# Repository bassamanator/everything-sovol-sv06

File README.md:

# Everything Sovol SV06

A repository containing specifications of the Sovol SV06 3D printer parts, as well as links to aftermarket replacement parts.

You can assume that all information herein is accurate unless stated otherwise.

You can also contribute by making a [pull-request](https://github.com/bassamanator/everything-sovol-sv06/pulls), creating an [issue](https://github.com/bassamanator/everything-sovol-sv06/issues), or starting a [discussion](https://github.com/bassamanator/everything-sovol-sv06/discussions).

## Support Me ❤️

Please ⭐ star this repository! Support [open source](https://en.wikipedia.org/wiki/Open_source), and buy me a .

_Some of the links found on this page may be affiliate links._

# Contents

1. [Initial Setup Steps](./docs/initial-setup-checks.md)
2. [Print Head](./docs/hotend.md)
   - [PCB](./docs/hotend.md#pcb)
   - [Hotend](./docs/hotend.md#hotend)
     - [Heater Cartridge](./docs/hotend.md#heater-cartridge)
     - [Thermistor](./docs/hotend.md#thermistor)
     - [Heatbreak](./docs/hotend.md#heatbreak)
     - [Nozzle](./docs/hotend.md#nozzle)
   - [Filament Sensor](./docs/hotend.md#filament-sensor)
   - [Probe](./docs/hotend.md#probe)
   - _Fans_
   - [Extruder](./docs/hotend.md#extruder)
3. [Motherboard](./docs/motherboard.md)
4. [Motion System](./docs/motion-system.md)
   - [Lead Screws](./docs/motion-system.md#lead-screws)
   - [POM Nuts](./docs/motion-system.md#pom-nuts)
   - [Linear Motion Guide Rods](./docs/motion-system.md#linear-motion-guide-rods)
   - [Linear Bearings](./docs/motion-system.md#linear-bearings)
   - [Z Axis Couplers](./docs/motion-system.md#z-axis-couplers)
   - [Belts](./docs/motion-system.md#belts)
   - [Stepper Motors](./docs/motion-system.md#stepper-motors)
5. [Power Supply](./docs/power-supply.md)
6. [How To 🛠️](./docs/how-to.md)
7. [Links](./docs/links.md)
8. [Sample Prints 🍰](./images/prints/README.md)
9. [Printed Upgrades 🏗️](./parts/README.md#printed-parts)
10. [Modifications 🪚](https://github.com/bassamanator/everything-sovol-sv06/tree/mods)

# Stay Up-to-Date

This repository is a work in progress. Watch for updates:

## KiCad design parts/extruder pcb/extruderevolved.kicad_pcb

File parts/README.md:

# Printed Upgrades

Please use common sense regarding material choice. If you're printing something that is touching the heated bed or near the hotend, use `PETG`/`ABS`/`other high temperature filament`.

## Essential

### Bed Cable Strain Relief at the Motherboard Enclosure

I no longer recommend a part for this, as I did previously. I think it actually strains the cable which eventually leads to damaged wires, as I experienced.

### Bed Cable Strain Relief at the Bed

- Designer: [@braga3dprint](https://www.printables.com/@braga3dprint)
- Printer: SV06
- [Source](https://www.printables.com/model/452682-sovol-sv06-strain-relief)
- [Download](https://www.printables.com/model/452682-sovol-sv06-strain-relief/files)
- I prefer the flat version as it perfectly supports the cable and doesn't interfere with my part cooling duct.
- After you get the part in place, make sure your bed can move freely without the bed cable snagging at the printer base extrusions.

## Useful

### Frame Mounting Solution

- Designer: [@bassamanator](https://www.printables.com/@bassamanator)
- Printer: SV06 / Plus
- Download from [here](https://www.printables.com/model/431736-sovol-sv06plus-frame-mounting-solution-2040-extrus).

### Part Cooling Fan Duct

- Designer: [taeky](https://cults3d.com/en/users/taeky/3d-models)
- Printer: SV06 (taeky has a Plus version as well).
- **This is a paid model**.
- There is a V2 of this model as well, but the performance according to the designer is the same. I prefer this version because it holds the duct more securely to the extruder assembly.
- [Sovol SV06 fan duct 5015 - CFD optimized](https://cults3d.com/:1021376)

- Designer: [Leander Perez Blanco](https://www.printables.com/@LeanderPerezB_802715)
- Printer: SV06.
- I have not tested this duct yet, but it is CFD optimized as well.
- There is a 1 fan version as well.
- [The Amonite - Sovol SV06 Fan Duct Dual 5015 Blower Fan V4 ](https://www.printables.com/model/543502-the-amonite-sovol-sv06-fan-duct-dual-5015-blower-f)

### Extrusion Seals

- Designer: [@bassamanator](https://www.printables.com/@bassamanator)
- Printer: SV06 / Plus
- Download from [here](https://www.printables.com/model/385359-sovol-sv06plus-extrusion-seal).

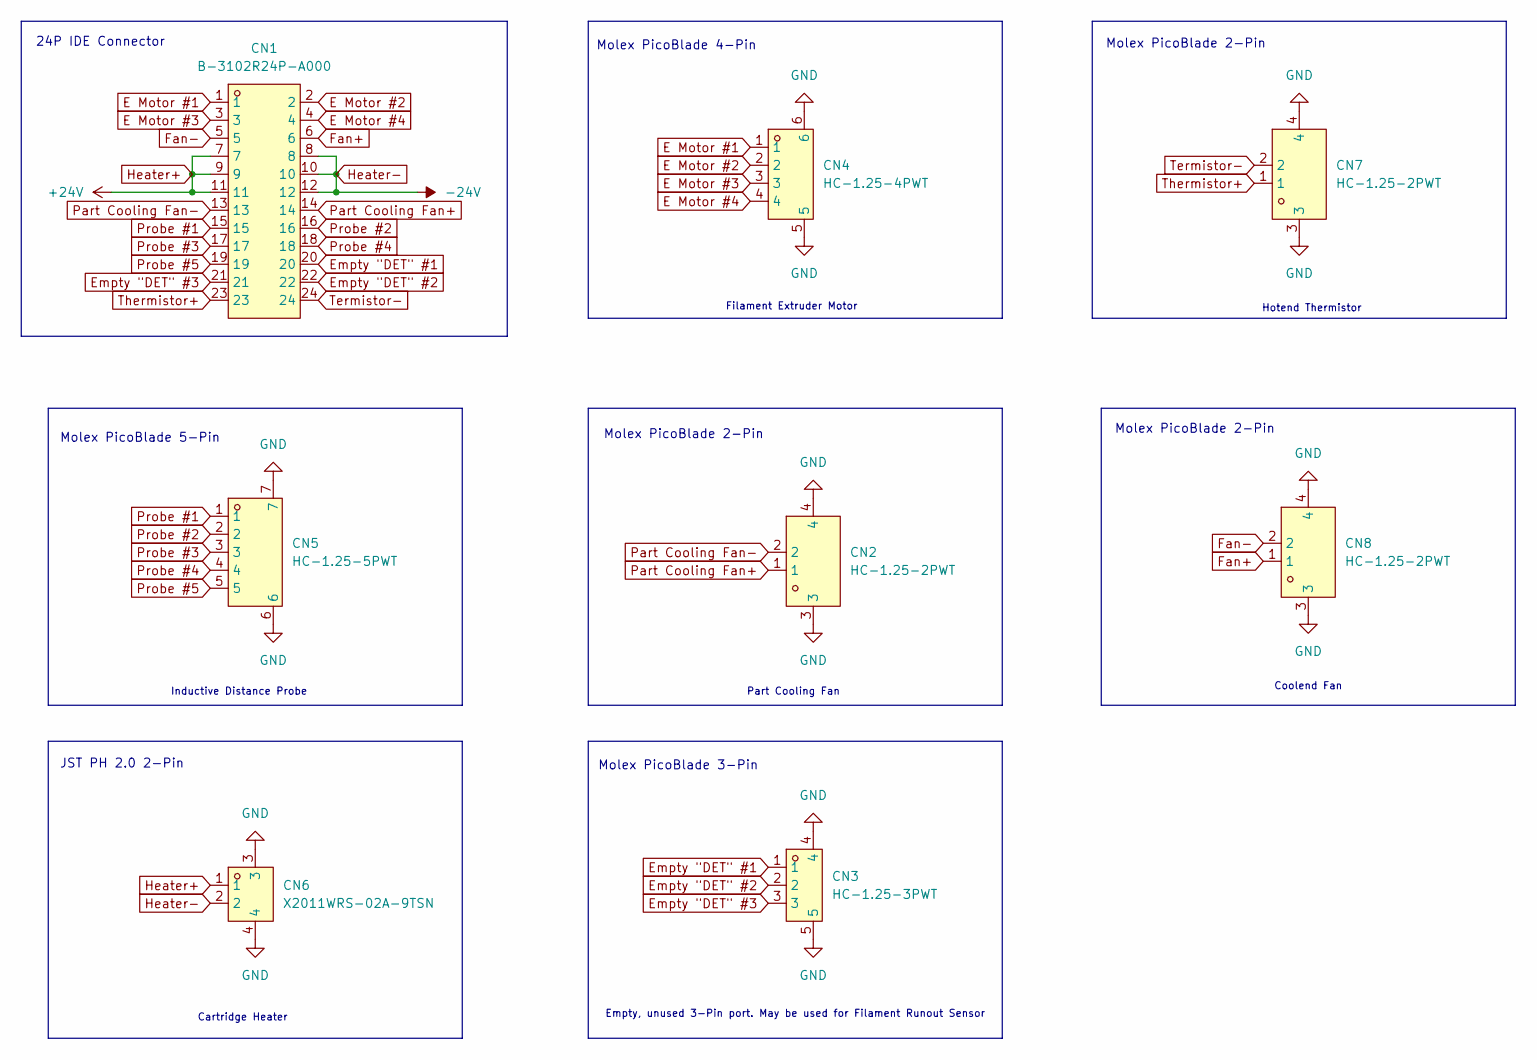
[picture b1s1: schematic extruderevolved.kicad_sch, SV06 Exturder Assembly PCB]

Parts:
CN1: B-3102R24P-A000; IDC-TH_24P-P2.00_B-3102R24P-A000; LCSC Part C383593
CN2, CN7, CN8: HC-1.25-2PWT; CONN-SMD_2P-P1.25-HC-1.25-2PWT; LCSC Part C2845379
CN3: HC-1.25-3PWT; CONN-SMD_HC-1.25-3PWT; LCSC Part C2845380
CN4: HC-1.25-4PWT; CONN-SMD_4P-P1.25-HC-1.25-4PWT; LCSC Part C2845381
CN5: HC-1.25-5PWT; CONN-SMD_5P-P1.25_HCTL_HC-1.25-5PWT; LCSC Part C2845382
CN6: X2011WRS-02A-9TSN; CONN-SMD_2P-P2.00_XKB_X2011WRS-02A-9TSN; LCSC Part C571320

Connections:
E Motor #1: CN1.1, CN4.1
E Motor #2: CN1.2, CN4.2
E Motor #3: CN1.3, CN4.3
E Motor #4: CN1.4, CN4.4
Empty "DET" #1: CN1.20, CN3.1
Empty "DET" #2: CN1.22, CN3.2
Empty "DET" #3: CN1.21, CN3.3
Fan+: CN1.6, CN8.1
Fan-: CN1.5, CN8.2
GND: CN2.3, CN2.4, CN3.4, CN3.5, CN4.5, CN4.6, CN5.6, CN5.7, CN6.3, CN6.4, CN7.3, CN7.4, CN8.3, CN8.4
Heater+: CN1.7, CN1.9, CN1.11, CN6.1
Heater-: CN1.8, CN1.10, CN1.12, CN6.2
Part Cooling Fan+: CN1.14, CN2.1
Part Cooling Fan-: CN1.13, CN2.2
Probe #1: CN1.15, CN5.1
Probe #2: CN1.16, CN5.2
Probe #3: CN1.17, CN5.3
Probe #4: CN1.18, CN5.4
Probe #5: CN1.19, CN5.5
Termistor-: CN1.24, CN7.2
Thermistor+: CN1.23, CN7.1

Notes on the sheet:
24P IDE Connector
Molex PicoBlade 5-Pin
Molex PicoBlade 4-Pin
Molex PicoBlade 2-Pin
JST PH 2.0 2-Pin
Inductive Distance Probe
Empty, unused 3-Pin port. May be used for Filament Runout Sensor
Part Cooling Fan
Filament Extruder Motor
Coolend Fan
Molex PicoBlade 3-Pin
Cartridge Heater
Hotend Thermistor

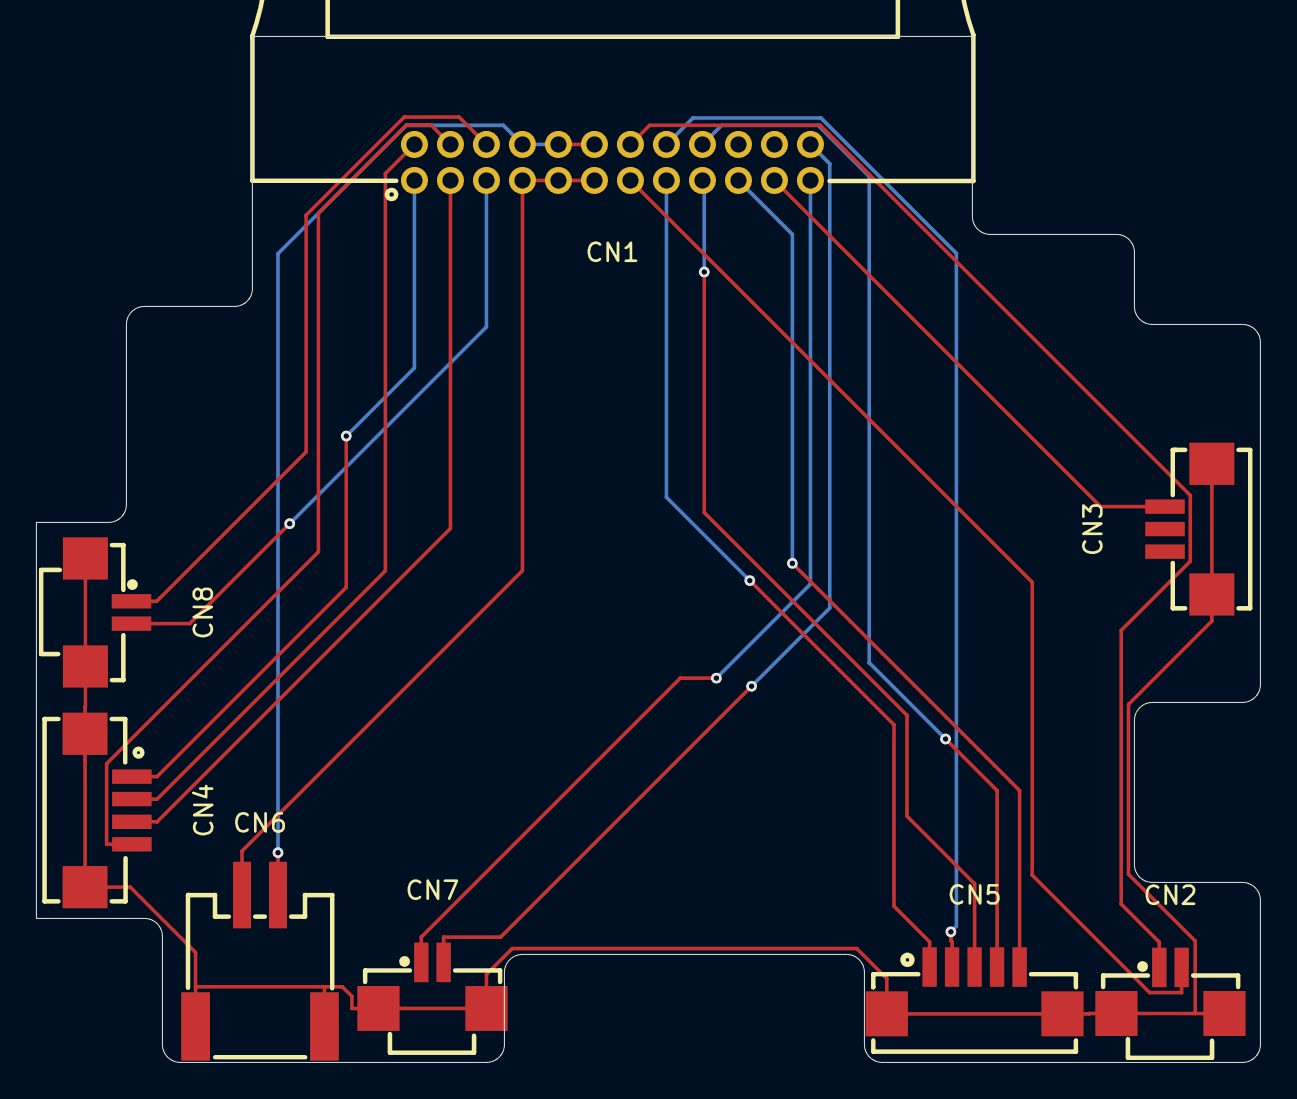
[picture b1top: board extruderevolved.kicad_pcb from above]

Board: 2 copper layers, 68.0 x 57.0 mm, 8 parts (0 on the bottom side), 21 nets.

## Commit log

2023-02-19 Changes.
2023-02-19 More changes.
2023-02-20 Adjusted README.md.
2023-02-22 Added motherboard picture.
2023-02-23 Added sovol repos.
2023-02-26 edited the readme.md
2023-02-27 Eoldev-Terry added lead screw and rod information to README.md (#6)
2023-02-28 Updated to-do list.
2023-03-03 Added Z coupler specs. Other styling changes in lead screw/rod section.
2023-03-03 More to do items.
2023-03-04 Heatblock specs and pictures.
2023-03-04 Heatblock spex and pictures.
2023-03-04 Heatblock spec and photos.
2023-03-05 13mm between the centers of the holes.
    It's looks like 13mm between the centers of the holes.
2023-03-05 Heatbreak spec and pictures.
    Heatbreak spec and pictures.
2023-03-05 Heatbreak spec and pictures.
    22mm long.
2023-03-05 Heatbreak spec and pictures.
    22mm.
2023-03-07 Edited images in Heatblock section.
2023-03-08 Updated to do list.
2023-03-13 Organized hotend section. Added filament sensor information.
2023-03-13 Added links for filament sensors.
2023-03-14 Updated filament sensor section.
2023-03-15 Updated runout sensor section.
2023-03-15 Added how to cable section; filament sensor.
2023-03-15 Added some random prints.
2023-03-19 Added PSU info.
2023-03-20 Update README.md
    Heatblock section.
2023-03-21 Added other psu cable pics.
2023-03-22 Added Heater, Thermistor and heatblock specifications
2023-03-22 Fixed formatting, added aftermarket options
2023-03-22 Fixed typo with M6 block, added how to use M6 nozzle instead of MK8
2023-03-22 Added Silicone Sock image
2023-03-22 Changed cartridge heater voltage to 24V from 12V and added link to source
2023-03-26 Update README.md
    Someone in the Reddit Sovol forum caught this. I checked my notes and the user was correct - it should read 355mm for X length.
2023-03-26 Added information for the heater cartridge mounting and removal
2023-03-28 Merging LimesKey-main: too many changes to enumerate.
2023-03-29 Correction to X length of rod (#20)
    Someone in the Reddit Sovol forum caught this. I checked my notes and the user was correct - it should read 355mm for X length.
2023-03-29 Added new thermistor aftermarket option as per request
2023-04-02 Added jump to sections.
2023-04-02 Fixed section links.
2023-04-02 Added useful parts section.
2023-04-02 Just some renaming.
2023-04-02 Fixed spelling, added useful prints section.
2023-04-02 Update README.md
    Removed to do section; taking up too much room, and not necessary.
2023-04-02 Updated outline.
2023-04-04 Added more sample prints.
2023-04-04 Confirmed extruder motor connection.
2023-04-09 Added psu model.
2023-04-09 Fixed XT60H model.
2023-04-09 Update README.md
    Fixed PSU table.
2023-04-20 Added probe section.
2023-04-20 Added link to purchase probe.
2023-04-20 Outline adjust.
2023-04-20 Probe picture size adjust.
2023-05-03 Options for heater cartridge and thermistor
    The thermistor and heater cartridge seem to be the same ones used on the Ender 3 S1 (Pro)
2023-06-12 Deleted many images. Added url to images.
2023-06-12 Prettified readme. Spelling fixes.
2023-06-14 Heatblock aftermarket link added.
2023-07-17 Adjust vscode project colours.
2023-08-01 Update README.md
    Thermistor section.
2023-08-01 Update README.md
    Heatbreak section notes.
2023-08-01 Update nozzle section.
2023-08-01 Update heatbreak section.
2023-08-01 Simplify heatblock section.
2023-08-01 Adjusted hierarchy.
2023-08-01 Adjusted layout, outline, hierarchy.
2023-08-01 Added link to purchase z coupler.
2023-08-01 Adjust Motherboard section.
2023-08-01 Adjust README.
2023-08-07 Add PSU Internal Fan Cable Connector specs.
2023-08-11 Adjust README.md: probe.
2023-08-11 Adjust README.md: fix heater cartridge wattage; add linear bearing specs.
2023-08-11 Create LICENSE
2023-08-11 Update issue templates
2023-08-12 Added stepper motor section; needs adjustement.
2023-08-12 Adjust Linear Bearings section.
2023-08-20 Added Plus nozzle info.
2023-08-24 Add more useful prints.
2023-08-26 Adjust Printed Parts section.
2023-08-26 Add initial steps section.
2023-08-26 Adjust initial steps.
2023-08-26 Create initialsteps.md.
2023-08-26 Adjust settings.
2023-08-30 Create howto.md. Add calibrate esteps.
2023-09-01 Adjust parts/README.md.
2023-09-01 Adjust parts/README.md. Add Y-axis stepper motor max height.
2023-09-01 Adjust parts/README.md: nozzle change.
2023-09-01 Include e-steps calibration tool.
2023-09-06 Add smooth idler specs.
2023-09-07 Adjust esteps howto.
2023-09-10 Add icons to readme outline. Add sample print.
2023-09-10 Update Update prints/README.md.
2023-10-14 Update README.md
    Newer heatblocks come with 3mm thermistor hole.
2023-10-23 added beacon tutorial
2023-10-23 added safe zone example
2023-10-23 added newline
2023-10-23 fixed spelling errors
2023-11-09 Update README.md
    Adjust resource links
2023-11-10 Add another option for filament sensor
2023-11-10 Fixup
2023-11-10 Add printer.cfg configuration for force_move command
2023-11-11 Update README.md
    Add mods link
2023-11-13 Added beacon probe setup (#32)
    * added beacon tutorial
    * added safe zone example
    * added newline
    * fixed spelling errors
    * Add printer.cfg configuration for force_move
    command
2023-11-13 Adjust mods readme.
2023-11-13 Adjust readme: remove beacon mod from main.
2023-11-14 Adjust filament sensor section.
2023-11-14 Adjust howto.md.
2023-11-23 Update howto.md.
2023-12-16 Add 3dtouch.
2023-12-16 Adjust readme mods.
2023-12-17 Update README.md
    Steppers
2023-12-24 Update howto.md
    Add sovol tech support playlist
2024-01-26 Adjust steppers.
2024-01-26 Adjust sections: lead screws, steppers.
2024-01-28 Adjust psu cable image.
2024-03-05 Add belt section.
2024-03-05 Adjust belts.
2024-03-06 Update howto.md: explain input shaping.
2024-03-06 Adjust parts readme.
2024-03-09 Add extruder section.
2024-03-29 Adjust outline, parts/README.md.
2024-03-29 Update README.md
    Added picture for ribboncable-pinout for probe
2024-03-29 Update README.md
    Uploaded pinoutribboncable.png and updated README.MD
2024-03-29 Probe pinout on ribbon-cable (#44)
    * Update README.md
    Added picture for ribboncable-pinout for probe
    * Add files via upload
    * Update README.md
    Uploaded pinoutribboncable.png and updated README.MD
2024-05-03 Fix: PCB connectors.
2024-06-06 add pcb files from kicad
2024-06-07 Add Extruder PCB Design Files & Schematics (#48)
    * add pcb files from kicad
    * Add files via upload
    * Add files via upload
2024-06-23 Rename folder.
2024-06-23 Add POM nuts to outline.
2024-07-30 upload new PCB files (#51)
    * Add files via upload
    * Add files via upload
2025-01-11 Adjust probe section.
2025-10-12 Fix broken .md links.
2025-12-19 Fix broken link.
2026-04-24 Adjust PSU section. Add markdownlinst.json.
2026-04-24 Adjust PSU section.
2026-04-24 Adjust hotend section.
2026-04-25 Maintainance.
2026-04-25 Add Back button at the top of all readmes.
2026-06-01 Add motherboard fan.
2026-06-02 Adjust FUNDING.yml.
